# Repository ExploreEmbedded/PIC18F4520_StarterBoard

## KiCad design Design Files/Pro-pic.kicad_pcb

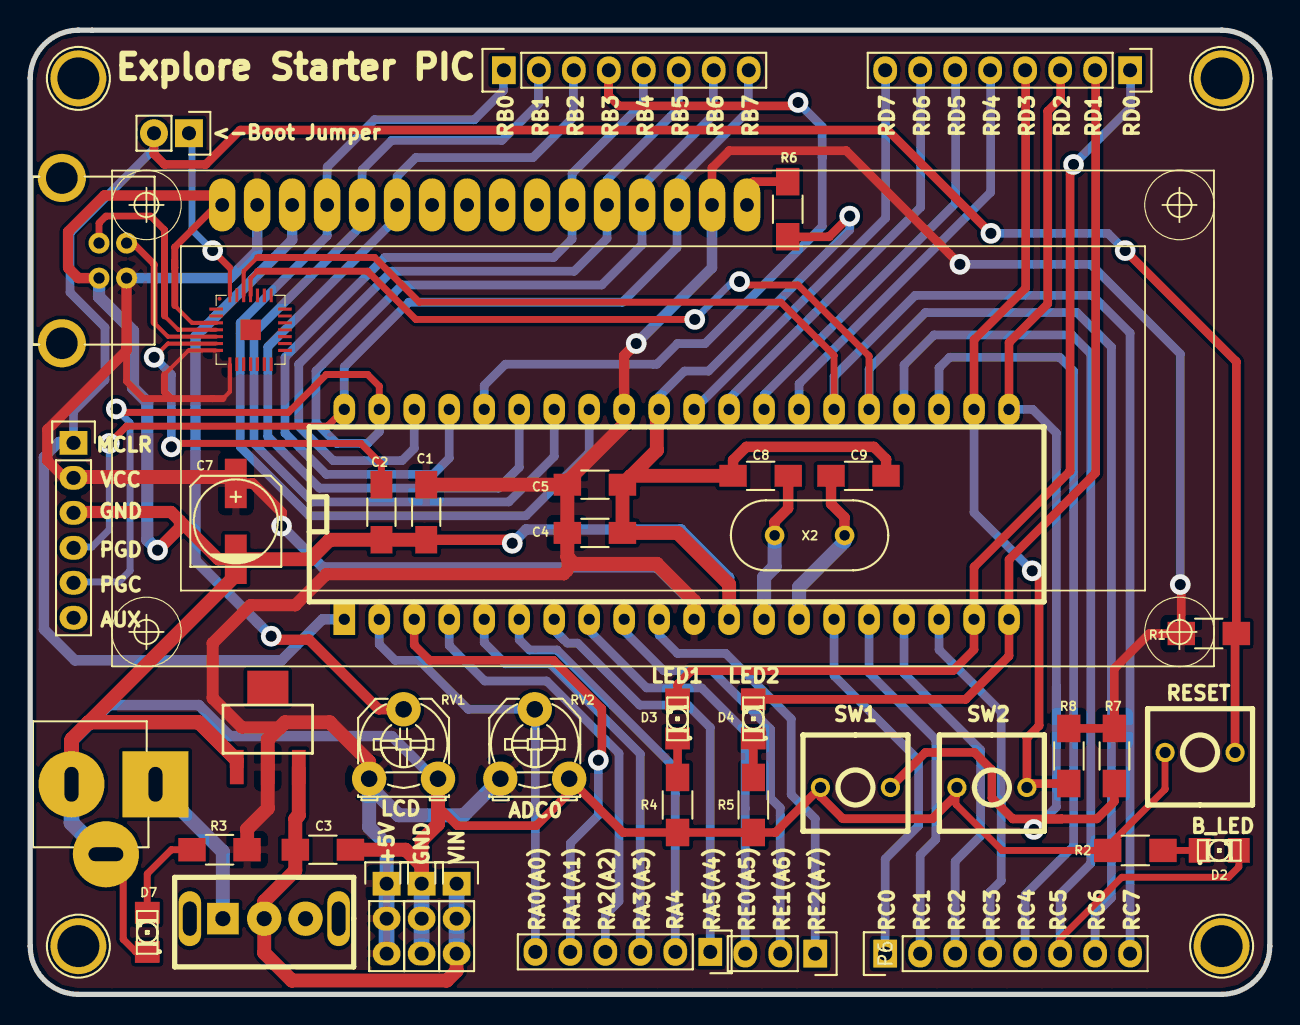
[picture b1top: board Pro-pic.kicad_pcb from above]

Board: 2 copper layers, 90.0 x 70.0 mm, 48 parts (1 on the bottom side), 50 nets.

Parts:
C1, C2, C3, C4, C5: 0.1uF; C_1206_HandSoldering
C7: 100uf, 25V; c_elec_6.3x4.5
C8, C9: 22pF; C_1206_HandSoldering
D2, D3, D4, D7: LED; LED-1206_NEW
J1: USB_2; USB_B
JP1: JUMPER; Pin_Header_Straight_1x02
K1: BARREL; DC_Jack
K2, K4, K5: CONN_3; Pin_Header_Straight_1x03
LCD1: LCD_2X16_SIL; lcd_2x16_led_backlight-HY-1602F
LOGO: LOGO (1)
P5: PA; Pin_Header_Straight_1x06
P6: PE; Pin_Header_Straight_1x03
P7: PC; Pin_Header_Straight_1x08
P8: PB; Pin_Header_Straight_1x08
P9: PD; Pin_Header_Straight_1x08
P10: ICSP; Pin_Header_Straight_1x06
P11, P12, P13, P14: CONN_1; 1pin
R1: 10K; R_1206_HandSoldering
R2, R4, R5: R; R_1206_HandSoldering
R3: 2.2K; R_1206_HandSoldering
R6: 1k; R_1206_HandSoldering
R7, R8: 10k; R_1206_HandSoldering
RV1: 10K-POT; Potentiometer_Triwood_RM-065
RV2: POT; Potentiometer_Triwood_RM-065
SW1: rst; SW_PUSH_SMALL_2pin_3D_xl
SW2: SPST; SlideSwitch_Big
SW3, SW4: SPST; SW_PUSH_SMALL_2pin_3D_xl
U1: 16F877A; DIP-40__600_ELL
U2: LM317AMDT; lm1117_xl
U3: CP2102; cp2102_xl2
X2: 20Mhz; HC-49V

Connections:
/+5V: C1.1, C4.2, C5.2, C7.1, J1.1, K2.1, K2.2, K2.3, LCD1.2, LCD1.15, P10.2, R1.2, R3.2, R7.2, R8.2, RV1.1, RV2.1, U1.11, U1.32, U2.2, U3.7, U3.8
/D4: LCD1.11, P8.5, U1.37
/D5: LCD1.12, P8.6, U1.38
/D6/PGC: LCD1.13, P8.7, P10.5, U1.39
/D7/PGD: LCD1.14, P8.8, P10.4, U1.40
/DC IN: C3.1, K5.1, K5.2, K5.3, SW2.2, U2.3
/E: LCD1.6, P8.3, U1.35
/L1: D2.1, P7.6, U1.24
/L2: D3.1, P9.1, U1.19
/L3: D4.1, P9.2, U1.20
/MCLR: JP1.2, P10.1, R1.1, SW1.1, U1.1
/RS: LCD1.4, P8.1, U1.33
/RW: LCD1.5, P8.2, U1.34
/S1: P9.3, R7.1, SW3.2, U1.21
/S2: P9.4, R8.1, SW4.2, U1.22
/rst: JP1.1, U3.28
/rxd: P7.8, U1.26, U3.26
/txd: P7.7, U1.25, U3.25
GND: C1.2, C2.1, C3.2, C4.1, C5.1, C7.2, C8.1, C9.1, D7.2, J1.4, K1.2, K1.3, K4.1, K4.2, K4.3, LCD1.1, P10.3, R2.1, R4.1, R5.1, R6.1, RV1.3, RV2.3, SW1.2, SW3.1, SW4.1, U1.12, U1.31, U2.1, U3.3
unnamed: C2.2, U3.6
unnamed: C8.2, U1.13, X2.2
unnamed: C9.2, U1.14, X2.1
unnamed: D2.2, R2.2
unnamed: D3.2, R4.2
unnamed: D4.2, R5.2
unnamed: D7.1, R3.1
unnamed: J1.2, U3.5
unnamed: J1.3, U3.4
unnamed: K1.1, SW2.1
unnamed: LCD1.3, RV1.2
unnamed: LCD1.16, R6.2
unnamed: P5.1, U1.7
unnamed: P5.2, U1.6
unnamed: P5.3, U1.5
unnamed: P5.4, U1.4
unnamed: P5.5, U1.3
unnamed: P5.6, RV2.2, U1.2
unnamed: P6.1, U1.10
unnamed: P6.2, U1.9
unnamed: P6.3, U1.8
unnamed: P7.1, U1.15
unnamed: P7.2, U1.16
unnamed: P7.3, U1.17
unnamed: P7.4, U1.18
unnamed: P7.5, U1.23
unnamed: P8.4, U1.36
unnamed: P9.5, U1.27
unnamed: P9.6, U1.28
unnamed: P9.7, U1.29
unnamed: P9.8, U1.30

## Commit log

2016-08-13 Added Board Test Code for Pic18f4520
    Added Board Test Code for Pic18f4520
2016-08-13 Added Bootloader ans sample code
    Added Bootloader ans sample code
2016-08-13 Added Eeprom Read Write Numbers
    Added Eeprom Read Write Numbers
2016-08-16 Design files added
